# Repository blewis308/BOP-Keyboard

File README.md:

# BOP-Keyboard

BOP stands for Big Ortho Project, a 6 row by 20 column ortholinear keyboard running off of the Teensy++2.0 Controller.

## Jump to...
* [What's included](#included-in-the-box)
* [Build Guide](#build-guide)
  
## REPO Contents:
* Plate File in `.dxf` format, perfect for creating a 3D printed case from.
* Various Pictures of the Prototype boards, also shown below.
* QMK Hex and firmware coming soontm

**Open Sourced PCB Files are for PERSONAL use only. Use for Commercial purposes without written permission is strictly prohibited.**

### Pictures

# Included in the Box:
#### Diodes - About 130x (120 needed)

#### Standoffs + Screws - M3 Size (10x Standoffs and 20x Screws)

#### Controller Headers - 2x 20 pin male and female headers

#### Stabilizers - 3x 2u Stabilizers

#### Rubber Feet - 8x Feet

#### Controller - 1x Teensy++2.0 Micro Controller

# Build Guide:
## Total Estimated Time: 4-5 hours

## Before you begin! 
#### Please test your board, some boards have shown signs of multiple switches actuating at the same time or switches that are shorting out with nearby ones. You can test this by using a multimeter in continuity mode and test each pin on the socket to pins in the rows. If anything is wrong, please contact me via Discord DM or email and I'll work with you to take care of the issue.

### Step 1: Diodes
#### Estimated Time: 2-3 hours
[This is a really good video on how to solder smd diodes](https://youtu.be/Jpj3tilIaik?t=187). I recommend you watch this before soldering.

Start by orienting the PCB so that you can read "Design by Fruitykeeb" straight on. Next, place a small amound of solder the pad opposite to the "K" on each of the diode locations.

Next, using tweezers or something similar, grab one diode and heat the bit of solder you just placed. Once the solder starts to melt, slide the diode into position. **Make sure the line on the diode is facing the "K" on the footprint. If it is not, key presses will not register!**

Finish the diodes by adding solder to the other pad. 

### Step 2: Headers
#### Estimated Time: 5-15 minutes

Keeping on the same side as the diodes, set the female headers onto the pcb. Making sure they are straight vertically, use tape to hold them in place. 

Flip the pcb over and solder the headers in place. **Make sure there are no shorts between pins.**

Next, place the male headers onto the controller. The USB port should be facing up, leave the longer legs up as well. Using tape to hold them im place, flip the controller over and solder them in. Again, make sure there are no shorts between pins. 

Press the controller in to test fit, but remove for flashing and switches.

### Step 3: Flashing the controller
#### Estimated Time: 5 minutes

My using [QMK Toolbox](https://github.com/qmk/qmk_toolbox), Open the default hex in the /keymaps/hex folder of this repo. 

In the MCU dropdown, select the `at90usb1286` option. Plug in the Teensy++2.0 and press the reset button at the bottom, then click `Flash` in the toolbox, this will flash the controller to the keymap you specify.

Press the controller in and using Via and tweezers, bridge the contacts where the switches would be to test each key. 

> If there is an issue where the last column spams the keys, there is a workaround detailed [here](#the-workaround).

### Step 4: Switches
#### Estimated Time: 45 mins - 1 hour.

**If you are using stabilizers, put your stabilizers in now.**

Start by pressing some switches into the plate. I recommend switches placed as in the picture below, but use enough so the plate doesn't fall down.

Flip the board over and solder in these first. **Note:** If you have a white pcb, the tolerances are tighter which makes pressing in switches harder. Double check that each switch is pressed fully in before soldering.

After these first switches are in, press in the remaining switches. Keep in mind that the top row, second column switch is rotated 180 from all the other switches.

Then, solder in the rest of the switches. Finally, press in the controller.

### Step 5: Standoffs and Bottom Plate
#### Estimated Time: 5 minutes

Start by placing a screw in the switch plate, then thread the standoff onto it. Repeat this for all 10 holes. Flip the whole board over and set the bottom plate on top; you shoudl be able to read "BOP".

Using a screw driver, screw in the remaining screws and then place the rubber feet around the edge of the board.

### Step 6: Enjoy!

Congratulations! You finished your BOP build! Add switches and start typing away!

## The Workaround:
If you have an issue with your board spamming the far right column of keys, use this workaround. 

On the bottom side of the controller, solder a short between pins C6 and C7. In the `config.h` file, change the last item in the `MATRIX_COL_PINS` array from C7 to C6.

Recompile the hex and reflash the MCU. This should fix the problem.

If this still does not work, clip the pins that go to ground from the micro controller.

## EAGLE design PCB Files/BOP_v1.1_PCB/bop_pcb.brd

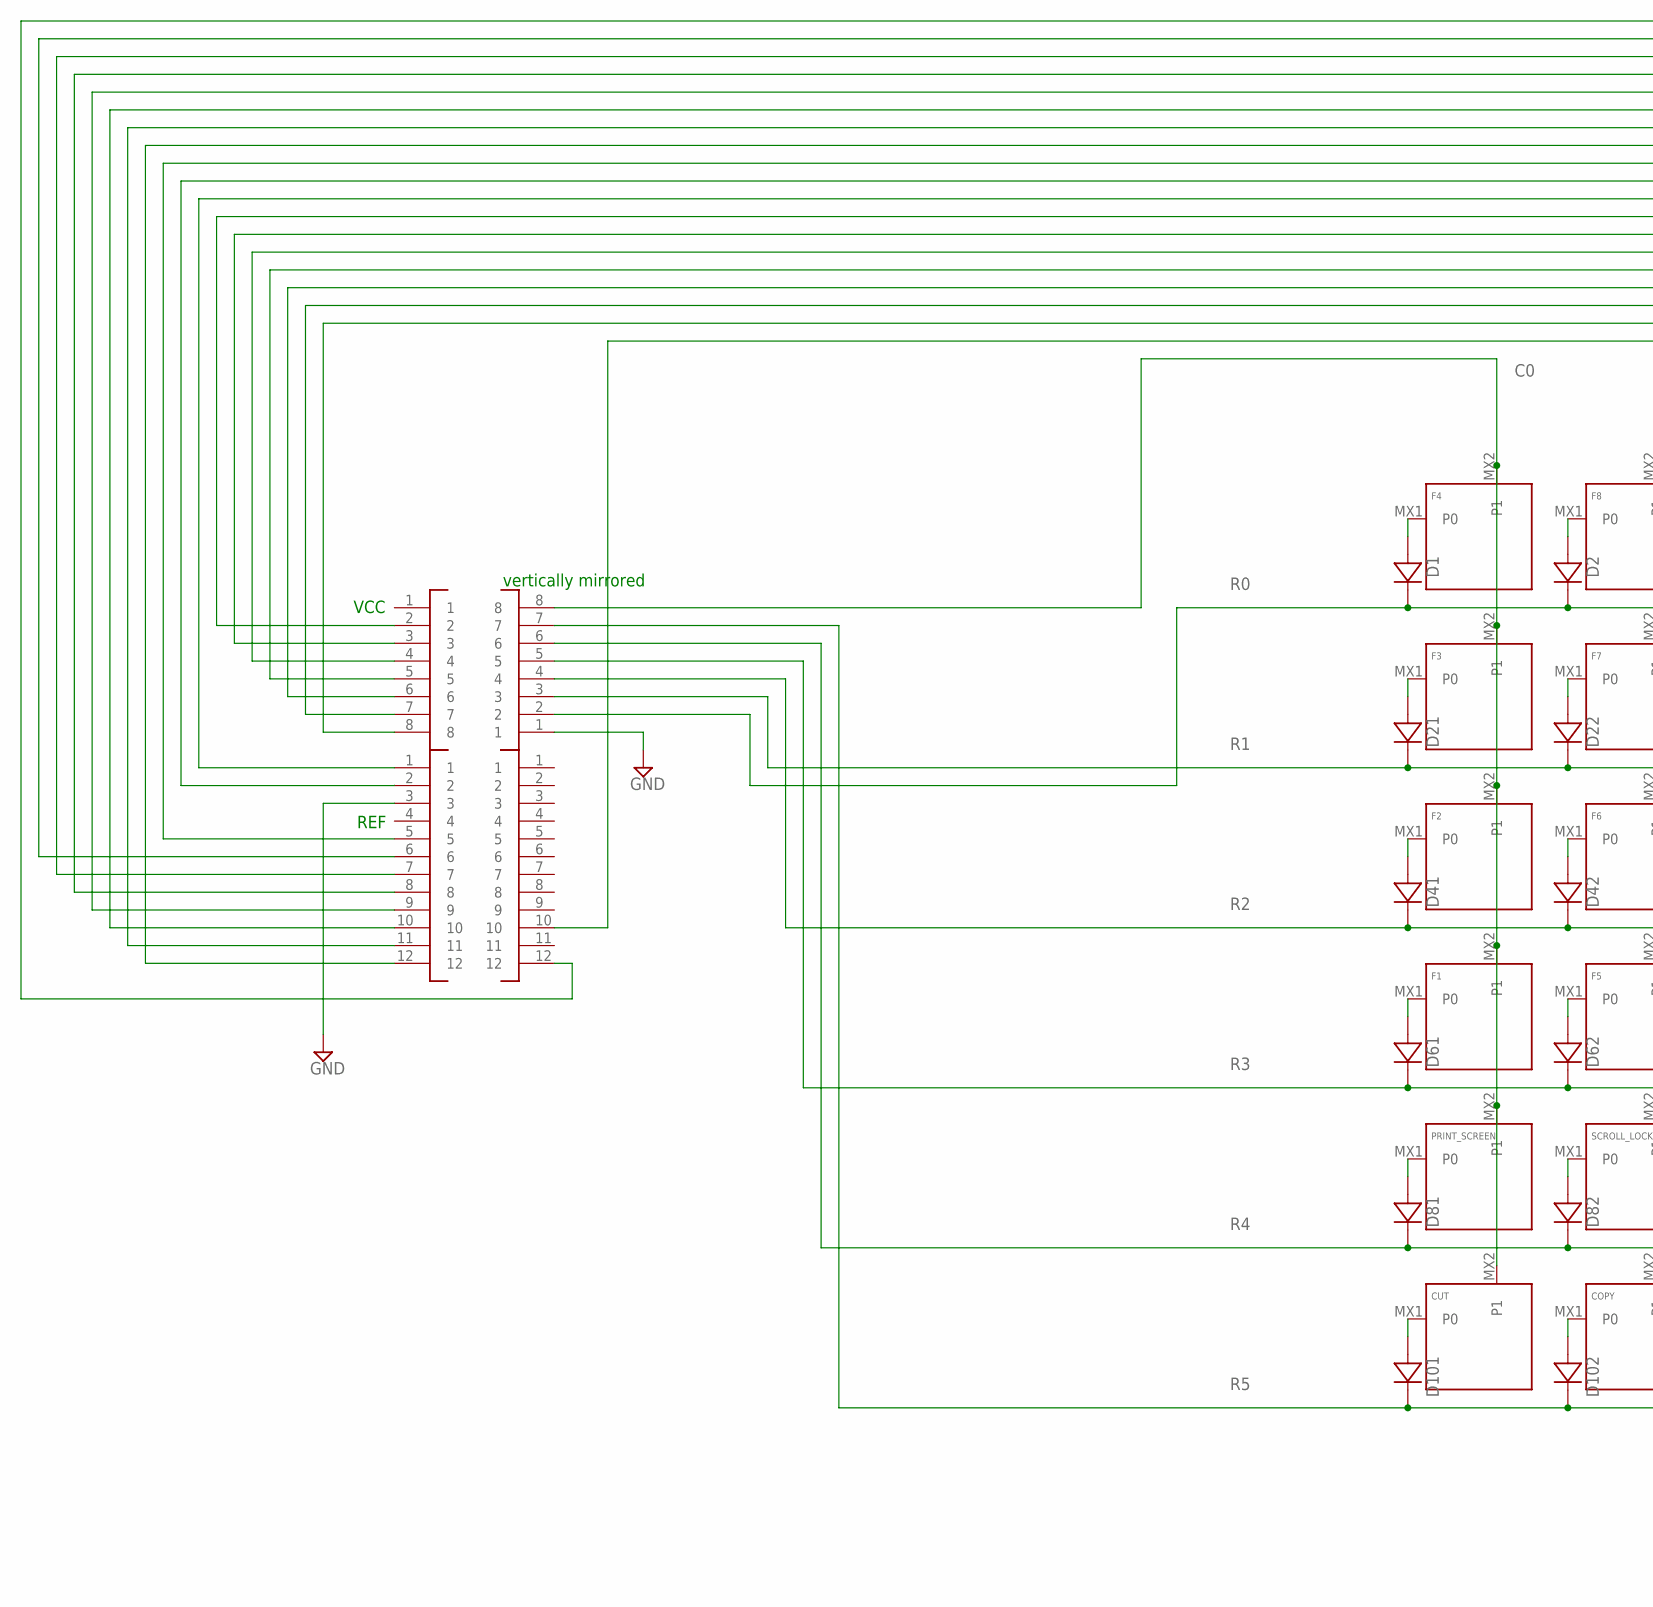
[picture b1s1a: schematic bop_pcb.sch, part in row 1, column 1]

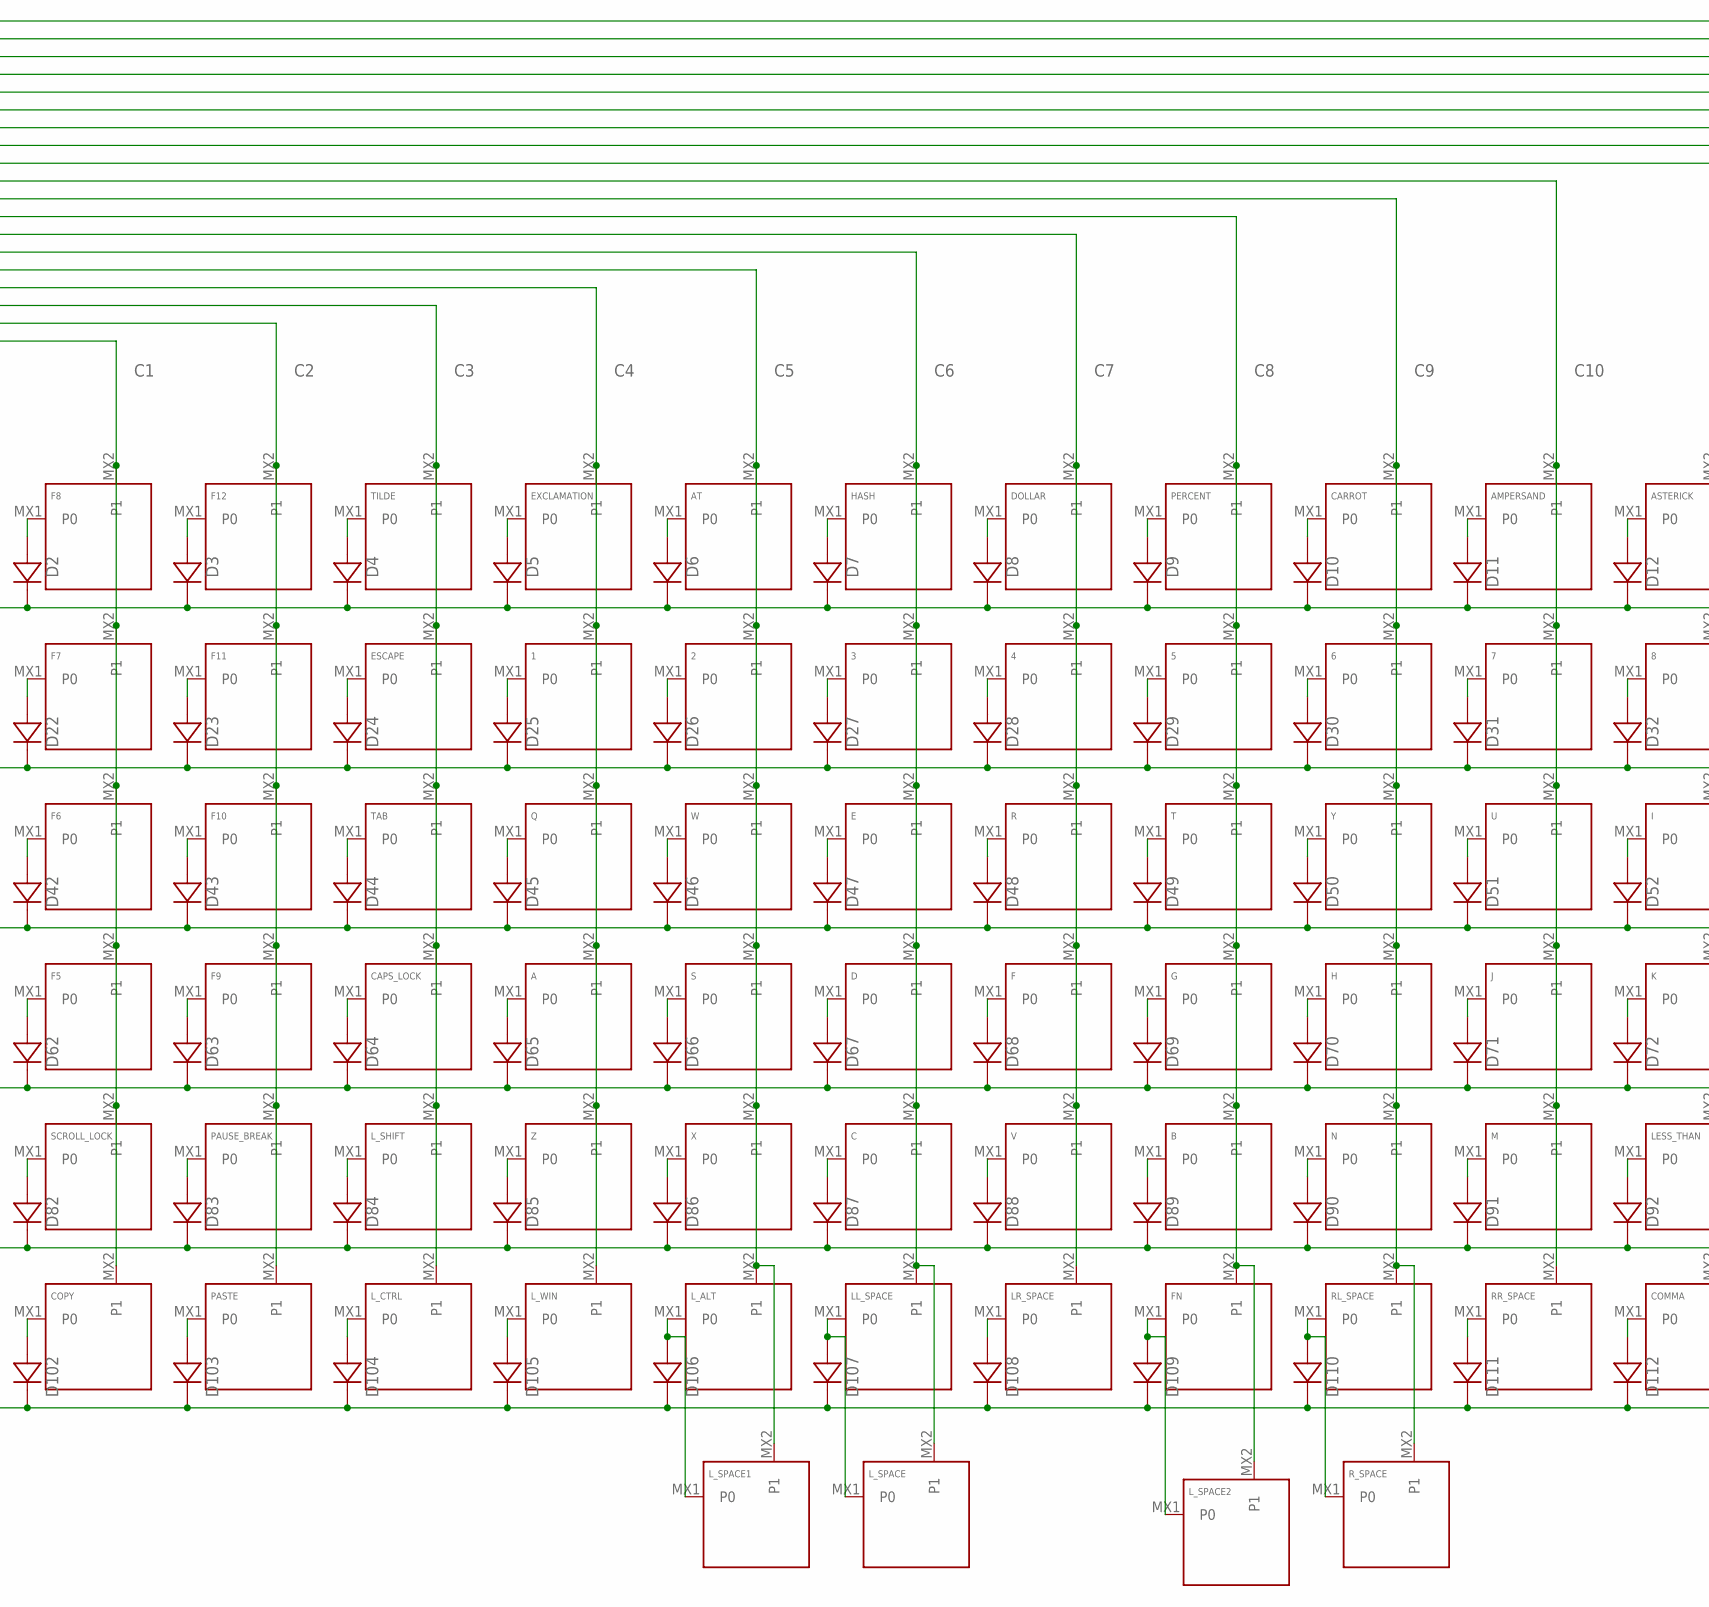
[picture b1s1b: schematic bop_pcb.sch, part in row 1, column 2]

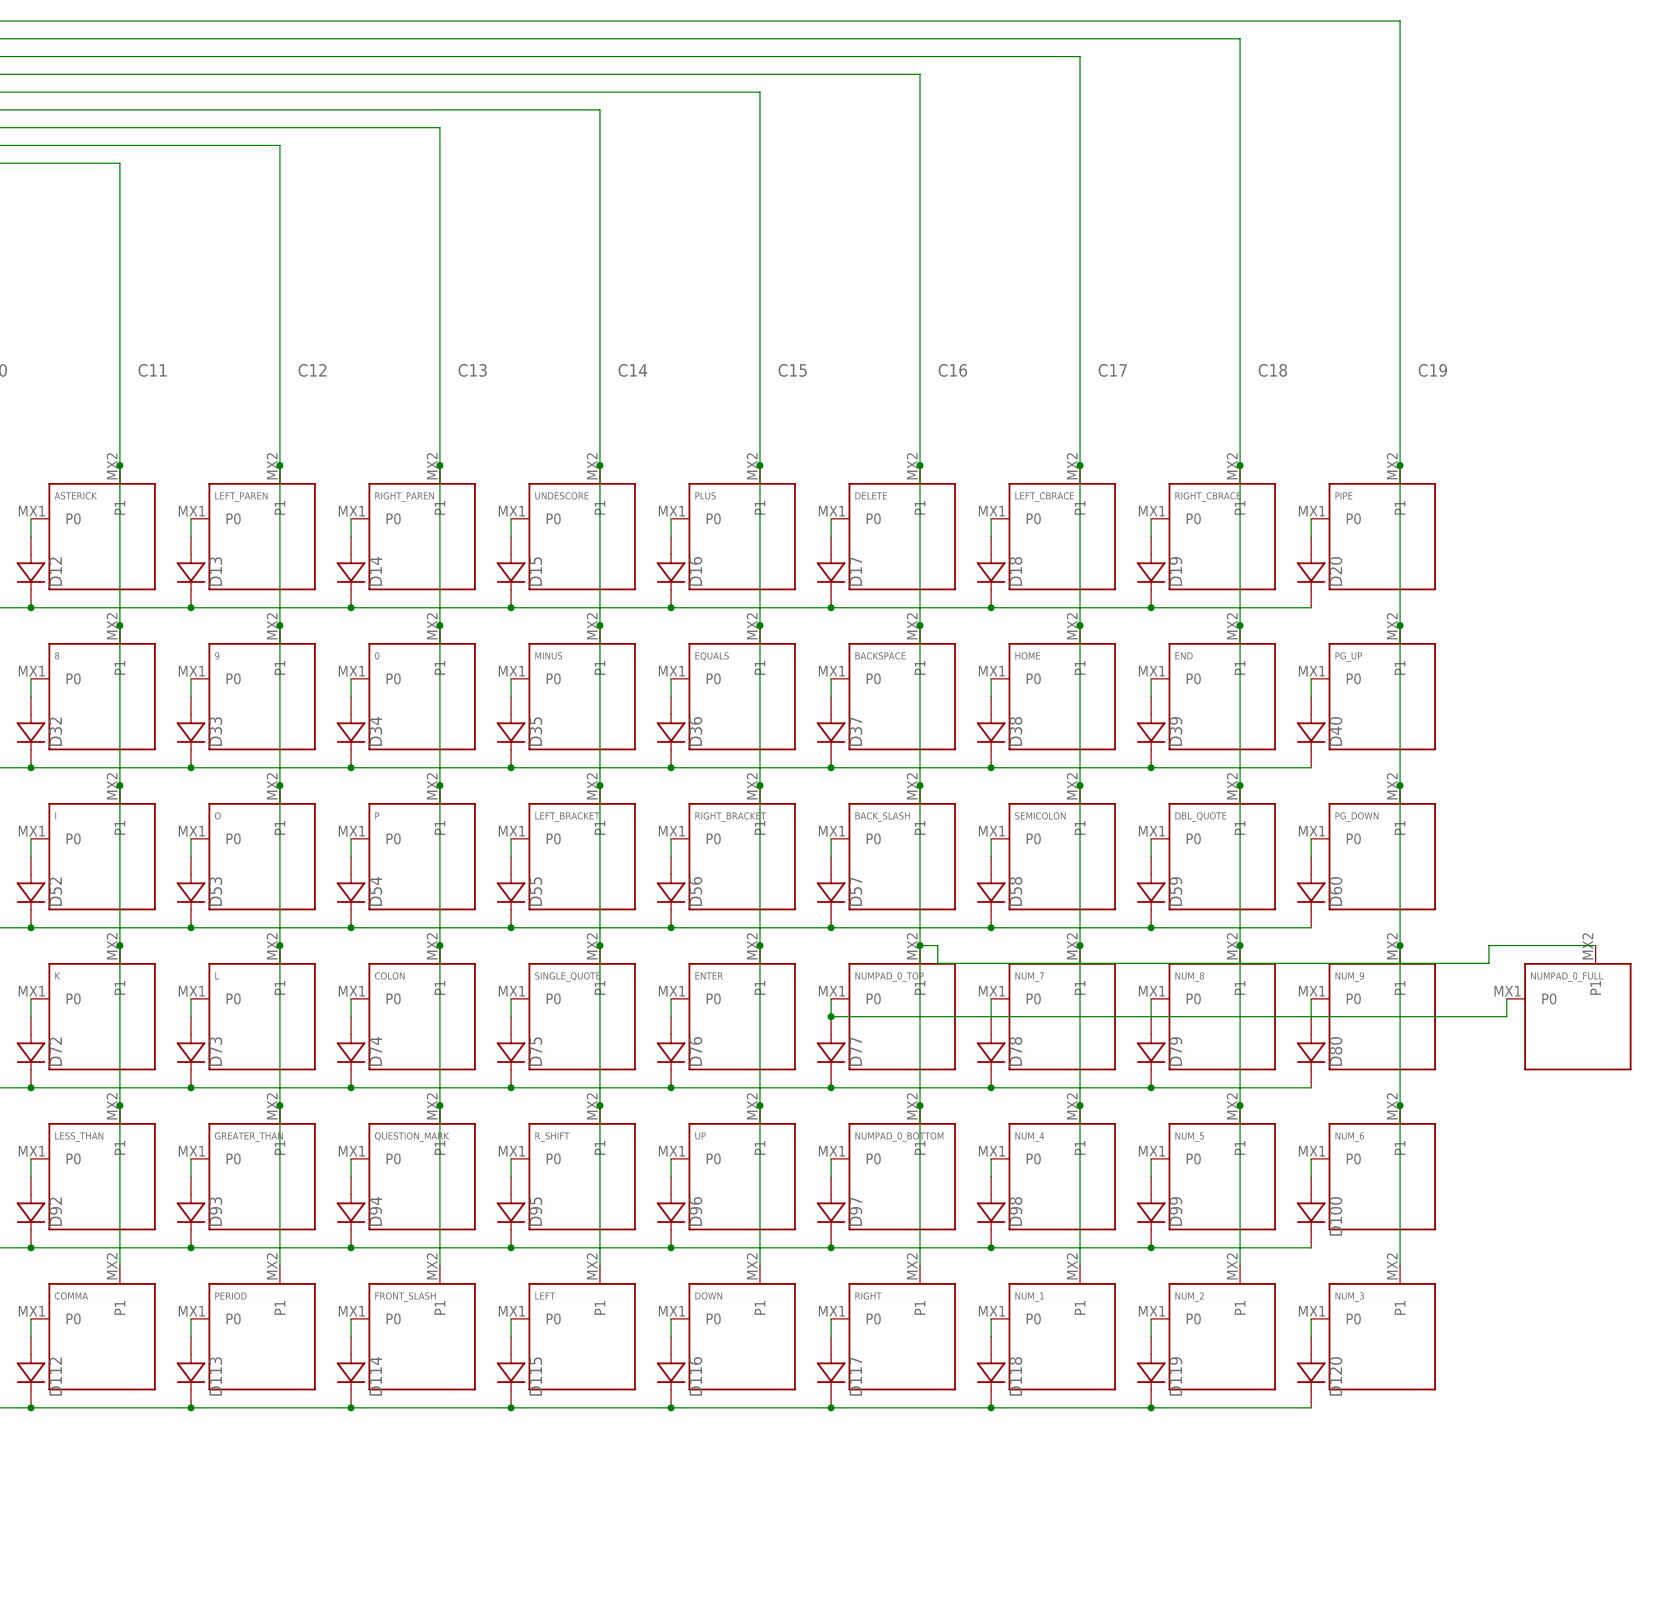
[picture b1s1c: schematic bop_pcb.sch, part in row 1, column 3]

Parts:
0, 1, 2, 3, 4, 5, 6, 7, 8, 9: KEYSWITCH-PLAIN-MX-1U; MX-1U
A: KEYSWITCH-PLAIN-MX-1U; MX-1U
AMPERSAND: KEYSWITCH-PLAIN-MX-1U; MX-1U
ASTERICK: KEYSWITCH-PLAIN-MX-1U; MX-1U
AT: KEYSWITCH-PLAIN-MX-1U; MX-1U
B: KEYSWITCH-PLAIN-MX-1U; MX-1U
BACKSPACE: KEYSWITCH-PLAIN-MX-1U; MX-1U
BACK_SLASH: KEYSWITCH-PLAIN-MX-1U; MX-1U
C: KEYSWITCH-PLAIN-MX-1U; MX-1U
CAPS_LOCK: KEYSWITCH-PLAIN-MX-1U; MX-1U
CARROT: KEYSWITCH-PLAIN-MX-1U; MX-1U
COLON: KEYSWITCH-PLAIN-MX-1U; MX-1U
COMMA: KEYSWITCH-PLAIN-MX-1U; MX-1U
COPY: KEYSWITCH-PLAIN-MX-1U; MX-1U
CUT: KEYSWITCH-PLAIN-MX-1U; MX-1U
D: KEYSWITCH-PLAIN-MX-1U; MX-1U
D1, D2, D3, D4, D5, D6, D7, D8, D9, D10, D11, D12, D13, D14, D15, D16, D17, D18, D19, D20, D21, D22, D23, D24, D25, D26, D27, D28, D29, D30, D31, D32, D33, D34, D35, D36, D37, D38, D39, D40, D41, D42, D43, D44, D45, D46, D47, D48, D49, D50, D51, D52, D53, D54, D55, D56, D57, D58, D59, D60, D61, D62, D63, D64, D65, D66, D67, D68, D69, D70, D71, D72, D73, D74, D75, D76, D77, D78, D79, D80, D81, D82, D83, D84, D85, D86, D87, D88, D89, D90, D91, D92, D93, D94, D95, D96, D97, D98, D99, D100, D101, D102, D103, D104, D105, D106, D107, D108, D109, D110, D111, D112, D113, D114, D115, D116, D117, D118, D119, D120: DIODE-SOD-123; SOD-123
DBL_QUOTE: KEYSWITCH-PLAIN-MX-1U; MX-1U
DELETE: KEYSWITCH-PLAIN-MX-1U; MX-1U
DOLLAR: KEYSWITCH-PLAIN-MX-1U; MX-1U
DOWN: KEYSWITCH-PLAIN-MX-1U; MX-1U
E: KEYSWITCH-PLAIN-MX-1U; MX-1U
END: KEYSWITCH-PLAIN-MX-1U; MX-1U
ENTER: KEYSWITCH-PLAIN-MX-1U; MX-1U
EQUALS: KEYSWITCH-PLAIN-MX-1U; MX-1U
ESCAPE: KEYSWITCH-PLAIN-MX-1U; MX-1U
EXCLAMATION: KEYSWITCH-PLAIN-MX-1U; MX-1U
F, F1, F2, F3, F4, F5, F6, F7, F8, F9, F10, F11, F12: KEYSWITCH-PLAIN-MX-1U; MX-1U
FN: KEYSWITCH-PLAIN-MX-1U; MX-1U
FRONT_SLASH: KEYSWITCH-PLAIN-MX-1U; MX-1U
G: KEYSWITCH-PLAIN-MX-1U; MX-1U
GREATER_THAN: KEYSWITCH-PLAIN-MX-1U; MX-1U
H: KEYSWITCH-PLAIN-MX-1U; MX-1U
HASH: KEYSWITCH-PLAIN-MX-1U; MX-1U
HOME: KEYSWITCH-PLAIN-MX-1U; MX-1U
I: KEYSWITCH-PLAIN-MX-1U; MX-1U
J: KEYSWITCH-PLAIN-MX-1U; MX-1U
J1, J2: HEADER-12X1-2.54-ROUND
K: KEYSWITCH-PLAIN-MX-1U; MX-1U
L: KEYSWITCH-PLAIN-MX-1U; MX-1U
LEFT: KEYSWITCH-PLAIN-MX-1U; MX-1U
LEFT_BRACKET: KEYSWITCH-PLAIN-MX-1U; MX-1U
LEFT_CBRACE: KEYSWITCH-PLAIN-MX-1U; MX-1U
LEFT_PAREN: KEYSWITCH-PLAIN-MX-1U; MX-1U
LESS_THAN: KEYSWITCH-PLAIN-MX-1U; MX-1U
LL_SPACE: KEYSWITCH-PLAIN-MX-1U; MX-1U
LR_SPACE: KEYSWITCH-PLAIN-MX-1U; MX-1U
L_ALT: KEYSWITCH-PLAIN-MX-1U; MX-1U
L_CTRL: KEYSWITCH-PLAIN-MX-1U; MX-1U
L_SHIFT: KEYSWITCH-PLAIN-MX-1U; MX-1U
L_SPACE, L_SPACE1, L_SPACE2: KEYSWITCH-PLAIN-MX-2U; MX-2U
L_WIN: KEYSWITCH-PLAIN-MX-1U; MX-1U
M: KEYSWITCH-PLAIN-MX-1U; MX-1U
MINUS: KEYSWITCH-PLAIN-MX-1U; MX-1U
N: KEYSWITCH-PLAIN-MX-1U; MX-1U
NUMPAD_0_BOTTOM, NUMPAD_0_TOP: KEYSWITCH-PLAIN-MX-1U; MX-1U
NUMPAD_0_FULL: KEYSWITCH-PLAIN-MX-2U; MX-2U
NUM_1, NUM_2, NUM_3, NUM_4, NUM_5, NUM_6, NUM_7, NUM_8, NUM_9: KEYSWITCH-PLAIN-MX-1U; MX-1U
O: KEYSWITCH-PLAIN-MX-1U; MX-1U
P: KEYSWITCH-PLAIN-MX-1U; MX-1U
PASTE: KEYSWITCH-PLAIN-MX-1U; MX-1U
PAUSE_BREAK: KEYSWITCH-PLAIN-MX-1U; MX-1U
PERCENT: KEYSWITCH-PLAIN-MX-1U; MX-1U
PERIOD: KEYSWITCH-PLAIN-MX-1U; MX-1U
PG_DOWN: KEYSWITCH-PLAIN-MX-1U; MX-1U
PG_UP: KEYSWITCH-PLAIN-MX-1U; MX-1U
PIPE: KEYSWITCH-PLAIN-MX-1U; MX-1U
PLUS: KEYSWITCH-PLAIN-MX-1U; MX-1U
PRINT_SCREEN: KEYSWITCH-PLAIN-MX-1U; MX-1U
Q: KEYSWITCH-PLAIN-MX-1U; MX-1U
QUESTION_MARK: KEYSWITCH-PLAIN-MX-1U; MX-1U
R: KEYSWITCH-PLAIN-MX-1U; MX-1U
RIGHT: KEYSWITCH-PLAIN-MX-1U; MX-1U
RIGHT_BRACKET: KEYSWITCH-PLAIN-MX-1U; MX-1U
RIGHT_CBRACE: KEYSWITCH-PLAIN-MX-1U; MX-1U
RIGHT_PAREN: KEYSWITCH-PLAIN-MX-1U; MX-1U
RL_SPACE: KEYSWITCH-PLAIN-MX-1U; MX-1U
RR_SPACE: KEYSWITCH-PLAIN-MX-1U; MX-1U
R_SHIFT: KEYSWITCH-PLAIN-MX-1U; MX-1U
R_SPACE: KEYSWITCH-PLAIN-MX-2U; MX-2U
S: KEYSWITCH-PLAIN-MX-1U; MX-1U
SCROLL_LOCK: KEYSWITCH-PLAIN-MX-1U; MX-1U
SEMICOLON: KEYSWITCH-PLAIN-MX-1U; MX-1U
SINGLE_QUOTE: KEYSWITCH-PLAIN-MX-1U; MX-1U
T: KEYSWITCH-PLAIN-MX-1U; MX-1U
TAB: KEYSWITCH-PLAIN-MX-1U; MX-1U
TILDE: KEYSWITCH-PLAIN-MX-1U; MX-1U
U: KEYSWITCH-PLAIN-MX-1U; MX-1U
U$1, U$2: HEADER-8X1-2.54
UNDESCORE: KEYSWITCH-PLAIN-MX-1U; MX-1U
UP: KEYSWITCH-PLAIN-MX-1U; MX-1U
V: KEYSWITCH-PLAIN-MX-1U; MX-1U
W: KEYSWITCH-PLAIN-MX-1U; MX-1U
X: KEYSWITCH-PLAIN-MX-1U; MX-1U
Y: KEYSWITCH-PLAIN-MX-1U; MX-1U
Z: KEYSWITCH-PLAIN-MX-1U; MX-1U

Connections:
C0: CUT.MX2 (P1), F1.MX2 (P1), F2.MX2 (P1), F3.MX2 (P1), F4.MX2 (P1), PRINT_SCREEN.MX2 (P1), U$2.8
C1: COPY.MX2 (P1), F5.MX2 (P1), F6.MX2 (P1), F7.MX2 (P1), F8.MX2 (P1), J1.10, SCROLL_LOCK.MX2 (P1)
C2: F9.MX2 (P1), F10.MX2 (P1), F11.MX2 (P1), F12.MX2 (P1), PASTE.MX2 (P1), PAUSE_BREAK.MX2 (P1), U$1.8
C3: CAPS_LOCK.MX2 (P1), ESCAPE.MX2 (P1), L_CTRL.MX2 (P1), L_SHIFT.MX2 (P1), TAB.MX2 (P1), TILDE.MX2 (P1), U$1.7
C4: 1.MX2 (P1), A.MX2 (P1), EXCLAMATION.MX2 (P1), L_WIN.MX2 (P1), Q.MX2 (P1), U$1.6, Z.MX2 (P1)
C5: 2.MX2 (P1), AT.MX2 (P1), L_ALT.MX2 (P1), L_SPACE1.MX2 (P1), S.MX2 (P1), U$1.5, W.MX2 (P1), X.MX2 (P1)
C6: 3.MX2 (P1), C.MX2 (P1), D.MX2 (P1), E.MX2 (P1), HASH.MX2 (P1), LL_SPACE.MX2 (P1), L_SPACE.MX2 (P1), U$1.4
C7: 4.MX2 (P1), DOLLAR.MX2 (P1), F.MX2 (P1), LR_SPACE.MX2 (P1), R.MX2 (P1), U$1.3, V.MX2 (P1)
C8: 5.MX2 (P1), B.MX2 (P1), FN.MX2 (P1), G.MX2 (P1), L_SPACE2.MX2 (P1), PERCENT.MX2 (P1), T.MX2 (P1), U$1.2
C9: 6.MX2 (P1), CARROT.MX2 (P1), H.MX2 (P1), J2.1, N.MX2 (P1), RL_SPACE.MX2 (P1), R_SPACE.MX2 (P1), Y.MX2 (P1)
C10: 7.MX2 (P1), AMPERSAND.MX2 (P1), J.MX2 (P1), J2.2, M.MX2 (P1), RR_SPACE.MX2 (P1), U.MX2 (P1)
C11: 8.MX2 (P1), ASTERICK.MX2 (P1), COMMA.MX2 (P1), I.MX2 (P1), J2.5, K.MX2 (P1), LESS_THAN.MX2 (P1)
C12: 9.MX2 (P1), GREATER_THAN.MX2 (P1), J2.12, L.MX2 (P1), LEFT_PAREN.MX2 (P1), O.MX2 (P1), PERIOD.MX2 (P1)
C13: 0.MX2 (P1), COLON.MX2 (P1), FRONT_SLASH.MX2 (P1), J2.11, P.MX2 (P1), QUESTION_MARK.MX2 (P1), RIGHT_PAREN.MX2 (P1)
C14: J2.10, LEFT.MX2 (P1), LEFT_BRACKET.MX2 (P1), MINUS.MX2 (P1), R_SHIFT.MX2 (P1), SINGLE_QUOTE.MX2 (P1), UNDESCORE.MX2 (P1)
C15: DOWN.MX2 (P1), ENTER.MX2 (P1), EQUALS.MX2 (P1), J2.9, PLUS.MX2 (P1), RIGHT_BRACKET.MX2 (P1), UP.MX2 (P1)
C16: BACKSPACE.MX2 (P1), BACK_SLASH.MX2 (P1), DELETE.MX2 (P1), J2.8, NUMPAD_0_BOTTOM.MX2 (P1), NUMPAD_0_FULL.MX2 (P1), NUMPAD_0_TOP.MX2 (P1), RIGHT.MX2 (P1)
C17: HOME.MX2 (P1), J2.7, LEFT_CBRACE.MX2 (P1), NUM_1.MX2 (P1), NUM_4.MX2 (P1), NUM_7.MX2 (P1), SEMICOLON.MX2 (P1)
C18: DBL_QUOTE.MX2 (P1), END.MX2 (P1), J2.6, NUM_2.MX2 (P1), NUM_5.MX2 (P1), NUM_8.MX2 (P1), RIGHT_CBRACE.MX2 (P1)
C19: J1.12, NUM_3.MX2 (P1), NUM_6.MX2 (P1), NUM_9.MX2 (P1), PG_DOWN.MX2 (P1), PG_UP.MX2 (P1), PIPE.MX2 (P1)
GND: J2.3, U$2.1
unnamed: D1.A, F4.MX1 (P0)
unnamed: D2.A, F8.MX1 (P0)
unnamed: D3.A, F12.MX1 (P0)
unnamed: D4.A, TILDE.MX1 (P0)
unnamed: D5.A, EXCLAMATION.MX1 (P0)
unnamed: AT.MX1 (P0), D6.A
unnamed: D7.A, HASH.MX1 (P0)
unnamed: D8.A, DOLLAR.MX1 (P0)
unnamed: D9.A, PERCENT.MX1 (P0)
unnamed: CARROT.MX1 (P0), D10.A
unnamed: AMPERSAND.MX1 (P0), D11.A
unnamed: ASTERICK.MX1 (P0), D12.A
unnamed: D13.A, LEFT_PAREN.MX1 (P0)
unnamed: D14.A, RIGHT_PAREN.MX1 (P0)
unnamed: D15.A, UNDESCORE.MX1 (P0)
unnamed: D16.A, PLUS.MX1 (P0)
unnamed: D17.A, DELETE.MX1 (P0)
unnamed: D18.A, LEFT_CBRACE.MX1 (P0)
unnamed: D19.A, RIGHT_CBRACE.MX1 (P0)
unnamed: D20.A, PIPE.MX1 (P0)
unnamed: D21.A, F3.MX1 (P0)
unnamed: D22.A, F7.MX1 (P0)
unnamed: D23.A, F11.MX1 (P0)
unnamed: D24.A, ESCAPE.MX1 (P0)
unnamed: 1.MX1 (P0), D25.A
unnamed: 2.MX1 (P0), D26.A
unnamed: 3.MX1 (P0), D27.A
unnamed: 4.MX1 (P0), D28.A
unnamed: 5.MX1 (P0), D29.A
unnamed: 6.MX1 (P0), D30.A
unnamed: 7.MX1 (P0), D31.A
unnamed: 8.MX1 (P0), D32.A
unnamed: 9.MX1 (P0), D33.A
unnamed: 0.MX1 (P0), D34.A
unnamed: D35.A, MINUS.MX1 (P0)
unnamed: D36.A, EQUALS.MX1 (P0)
unnamed: BACKSPACE.MX1 (P0), D37.A
unnamed: D38.A, HOME.MX1 (P0)
unnamed: D39.A, END.MX1 (P0)
unnamed: D40.A, PG_UP.MX1 (P0)
unnamed: D41.A, F2.MX1 (P0)
unnamed: D42.A, F6.MX1 (P0)
unnamed: D43.A, F10.MX1 (P0)
unnamed: D44.A, TAB.MX1 (P0)
unnamed: D45.A, Q.MX1 (P0)
unnamed: D46.A, W.MX1 (P0)
unnamed: D47.A, E.MX1 (P0)
unnamed: D48.A, R.MX1 (P0)
unnamed: D49.A, T.MX1 (P0)
unnamed: D50.A, Y.MX1 (P0)
unnamed: D51.A, U.MX1 (P0)
unnamed: D52.A, I.MX1 (P0)
unnamed: D53.A, O.MX1 (P0)
unnamed: D54.A, P.MX1 (P0)
unnamed: D55.A, LEFT_BRACKET.MX1 (P0)
unnamed: D56.A, RIGHT_BRACKET.MX1 (P0)
unnamed: BACK_SLASH.MX1 (P0), D57.A
unnamed: D58.A, SEMICOLON.MX1 (P0)
unnamed: D59.A, DBL_QUOTE.MX1 (P0)
unnamed: D60.A, PG_DOWN.MX1 (P0)
unnamed: D61.A, F1.MX1 (P0)
unnamed: D62.A, F5.MX1 (P0)
unnamed: D63.A, F9.MX1 (P0)
unnamed: CAPS_LOCK.MX1 (P0), D64.A
unnamed: A.MX1 (P0), D65.A
unnamed: D66.A, S.MX1 (P0)
unnamed: D.MX1 (P0), D67.A
unnamed: D68.A, F.MX1 (P0)
unnamed: D69.A, G.MX1 (P0)
unnamed: D70.A, H.MX1 (P0)
unnamed: D71.A, J.MX1 (P0)
unnamed: D72.A, K.MX1 (P0)
unnamed: D73.A, L.MX1 (P0)
unnamed: COLON.MX1 (P0), D74.A
unnamed: D75.A, SINGLE_QUOTE.MX1 (P0)
unnamed: D76.A, ENTER.MX1 (P0)
unnamed: D77.A, NUMPAD_0_FULL.MX1 (P0), NUMPAD_0_TOP.MX1 (P0)
unnamed: D79.A, NUM_8.MX1 (P0)
unnamed: D80.A, NUM_9.MX1 (P0)
unnamed: D81.A, PRINT_SCREEN.MX1 (P0)
unnamed: D82.A, SCROLL_LOCK.MX1 (P0)
unnamed: D83.A, PAUSE_BREAK.MX1 (P0)
unnamed: D84.A, L_SHIFT.MX1 (P0)
unnamed: D85.A, Z.MX1 (P0)
unnamed: D86.A, X.MX1 (P0)
unnamed: C.MX1 (P0), D87.A
unnamed: D88.A, V.MX1 (P0)
unnamed: B.MX1 (P0), D89.A
unnamed: D90.A, N.MX1 (P0)
unnamed: D91.A, M.MX1 (P0)
unnamed: D92.A, LESS_THAN.MX1 (P0)
unnamed: D93.A, GREATER_THAN.MX1 (P0)
unnamed: D94.A, QUESTION_MARK.MX1 (P0)
unnamed: D95.A, R_SHIFT.MX1 (P0)
unnamed: D96.A, UP.MX1 (P0)
unnamed: D97.A, NUMPAD_0_BOTTOM.MX1 (P0)
unnamed: D98.A, NUM_4.MX1 (P0)
unnamed: D99.A, NUM_5.MX1 (P0)
unnamed: D100.A, NUM_6.MX1 (P0)
unnamed: CUT.MX1 (P0), D101.A
unnamed: COPY.MX1 (P0), D102.A
unnamed: D103.A, PASTE.MX1 (P0)
unnamed: D104.A, L_CTRL.MX1 (P0)
unnamed: D105.A, L_WIN.MX1 (P0)
unnamed: D106.A, L_ALT.MX1 (P0), L_SPACE1.MX1 (P0)
unnamed: D107.A, LL_SPACE.MX1 (P0), L_SPACE.MX1 (P0)
unnamed: D108.A, LR_SPACE.MX1 (P0)
unnamed: D109.A, FN.MX1 (P0), L_SPACE2.MX1 (P0)
unnamed: D110.A, RL_SPACE.MX1 (P0), R_SPACE.MX1 (P0)
unnamed: D111.A, RR_SPACE.MX1 (P0)
unnamed: COMMA.MX1 (P0), D112.A
unnamed: D113.A, PERIOD.MX1 (P0)
unnamed: D114.A, FRONT_SLASH.MX1 (P0)
unnamed: D115.A, LEFT.MX1 (P0)
unnamed: D116.A, DOWN.MX1 (P0)
unnamed: D117.A, RIGHT.MX1 (P0)
unnamed: D118.A, NUM_1.MX1 (P0)
unnamed: D119.A, NUM_2.MX1 (P0)
unnamed: D120.A, NUM_3.MX1 (P0)
unnamed: D78.A, NUM_7.MX1 (P0)
R0: D1.C, D2.C, D3.C, D4.C, D5.C, D6.C, D7.C, D8.C, D9.C, D10.C, D11.C, D12.C, D13.C, D14.C, D15.C, D16.C, D17.C, D18.C, D19.C, D20.C, U$2.2
R1: D21.C, D22.C, D23.C, D24.C, D25.C, D26.C, D27.C, D28.C, D29.C, D30.C, D31.C, D32.C, D33.C, D34.C, D35.C, D36.C, D37.C, D38.C, D39.C, D40.C, U$2.3
R2: D41.C, D42.C, D43.C, D44.C, D45.C, D46.C, D47.C, D48.C, D49.C, D50.C, D51.C, D52.C, D53.C, D54.C, D55.C, D56.C, D57.C, D58.C, D59.C, D60.C, U$2.4
R3: D61.C, D62.C, D63.C, D64.C, D65.C, D66.C, D67.C, D68.C, D69.C, D70.C, D71.C, D72.C, D73.C, D74.C, D75.C, D76.C, D77.C, D78.C, D79.C, D80.C, U$2.5
R4: D81.C, D82.C, D83.C, D84.C, D85.C, D86.C, D87.C, D88.C, D89.C, D90.C, D91.C, D92.C, D93.C, D94.C, D95.C, D96.C, D97.C, D98.C, D99.C, D100.C, U$2.6
R5: D101.C, D102.C, D103.C, D104.C, D105.C, D106.C, D107.C, D108.C, D109.C, D110.C, D111.C, D112.C, D113.C, D114.C, D115.C, D116.C, D117.C, D118.C, D119.C, D120.C, U$2.7

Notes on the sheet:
VCC
REF
vertically mirrored

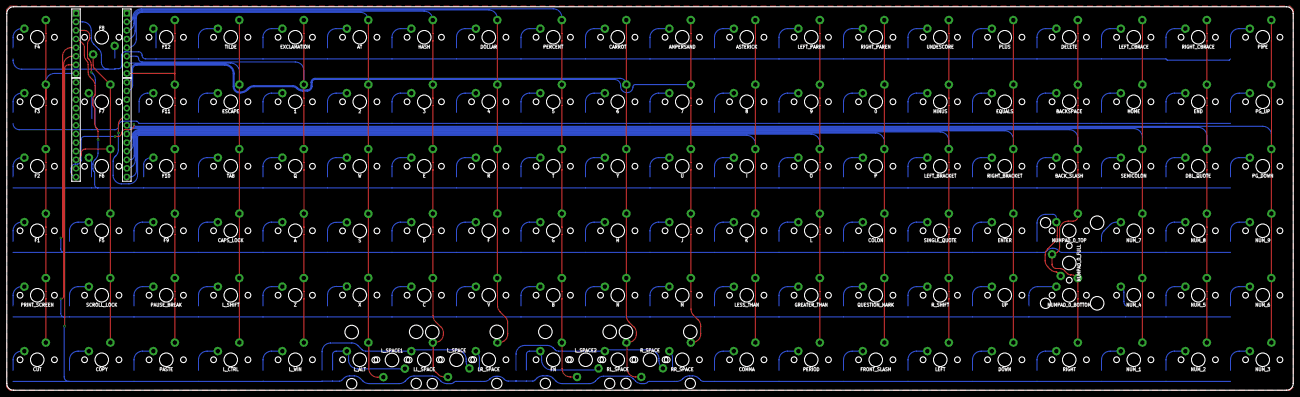
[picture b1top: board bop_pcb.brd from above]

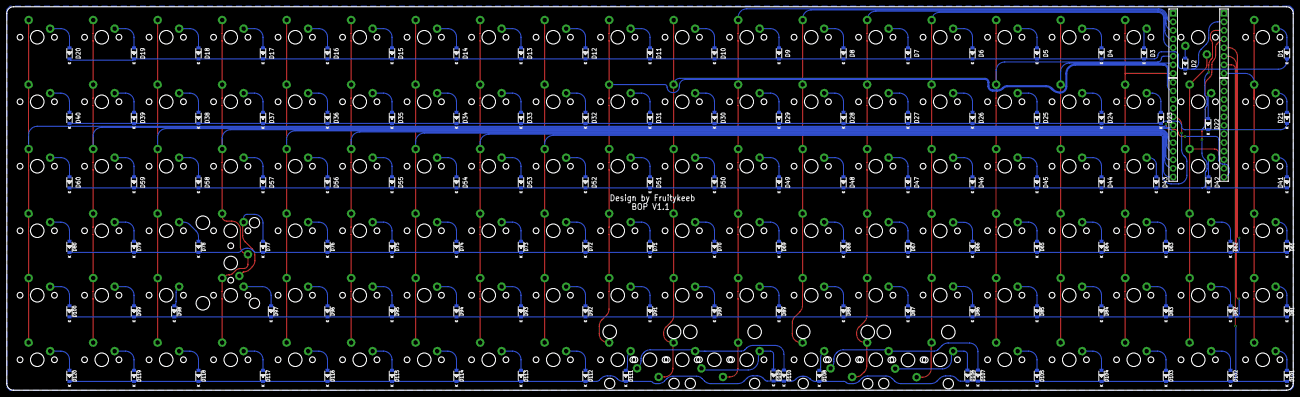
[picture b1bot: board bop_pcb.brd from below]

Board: 2 copper layers, 379.9 x 113.2 mm, 249 parts (120 on the bottom side), 147 nets.

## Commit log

2021-04-14 Updated plate and pictures
2021-05-11 Added keymap and hex
    Default keymap and default compiled hex
2021-05-11 readability
2021-05-12 Added sudsack keymap
2021-05-18 added c6 fix hex
2021-06-01 Fix Default Number pad & LAYER's
    Changed Default Number pad keys from KC to KC_KP to achieve expected function.
    Also changed KEYMAP to LAYER to bring better parity with QMK standards.
2021-06-02 Add VIA and basic Unicode support
    Started implementing VIA and basic Unicode support for the VIA profile.
2021-06-02 Fix Via layout
2021-06-02 Multi layout support
    Added layout options for 2u long keys on appropriate places on board
2021-12-17 open sourced
2022-02-23 added v1.1 pcb
